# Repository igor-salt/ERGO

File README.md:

Взято отсюда: https://github.com/ergonautkb/one Доработано и исправлено

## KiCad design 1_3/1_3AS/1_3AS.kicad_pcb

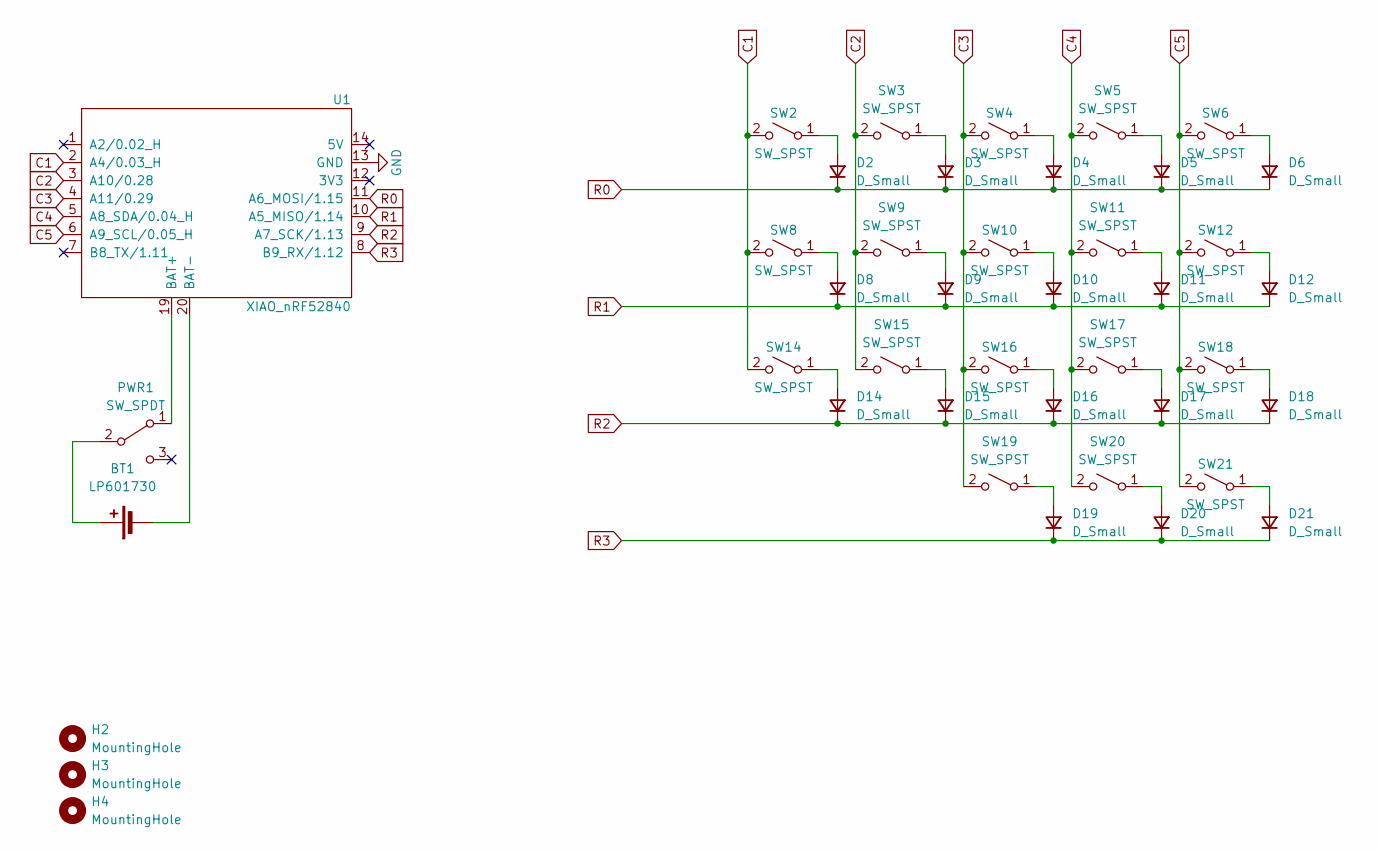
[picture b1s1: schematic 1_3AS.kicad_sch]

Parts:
BT1: LP601730; lp601730
D2, D3, D4, D5, D6, D8, D9, D10, D11, D12, D14, D15, D16, D17, D18, D19, D20, D21: D_Small; Diode_TH_SMD_DUAL
H2, H3, H4: MountingHole; Hole_5.7mm
PWR1: SW_SPDT; MSK-12C02_DUAL
SW2, SW3, SW4, SW5, SW6, SW8, SW9, SW10, SW11, SW12, SW14, SW15, SW16, SW17, SW18, SW19, SW20, SW21: SW_SPST; KS-27_KS-33_Hotswap_1U_DUAL
U1: XIAO_nRF52840; XIAO_nRF52840_DUAL_WINDOW_NO_CAP

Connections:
C1: SW2.2 (B), SW8.2 (B), SW14.2 (B), U1.2 (A4/0.03_H)
C2: SW3.2 (B), SW9.2 (B), SW15.2 (B), U1.3 (A10/0.28)
C3: SW4.2 (B), SW10.2 (B), SW16.2 (B), SW19.2 (B), U1.4 (A11/0.29)
C4: SW5.2 (B), SW11.2 (B), SW17.2 (B), SW20.2 (B), U1.5 (A8_SDA/0.04_H)
C5: SW6.2 (B), SW12.2 (B), SW18.2 (B), SW21.2 (B), U1.6 (A9_SCL/0.05_H)
GND: U1.13 (GND)
unnamed: BT1.1 (+), PWR1.2 (B)
unnamed: BT1.2 (-), U1.20 (BAT-)
unnamed: D2.2 (A), SW2.1 (A)
unnamed: D3.2 (A), SW3.1 (A)
unnamed: D4.2 (A), SW4.1 (A)
unnamed: D5.2 (A), SW5.1 (A)
unnamed: D6.2 (A), SW6.1 (A)
unnamed: D8.2 (A), SW8.1 (A)
unnamed: D9.2 (A), SW9.1 (A)
unnamed: D10.2 (A), SW10.1 (A)
unnamed: D11.2 (A), SW11.1 (A)
unnamed: D12.2 (A), SW12.1 (A)
unnamed: D14.2 (A), SW14.1 (A)
unnamed: D15.2 (A), SW15.1 (A)
unnamed: D16.2 (A), SW16.1 (A)
unnamed: D17.2 (A), SW17.1 (A)
unnamed: D18.2 (A), SW18.1 (A)
unnamed: D19.2 (A), SW19.1 (A)
unnamed: D20.2 (A), SW20.1 (A)
unnamed: D21.2 (A), SW21.1 (A)
unnamed: PWR1.1 (A), U1.19 (BAT+)
R0: D2.1 (K), D3.1 (K), D4.1 (K), D5.1 (K), D6.1 (K), U1.11 (A6_MOSI/1.15)
R1: D8.1 (K), D9.1 (K), D10.1 (K), D11.1 (K), D12.1 (K), U1.10 (A5_MISO/1.14)
R2: D14.1 (K), D15.1 (K), D16.1 (K), D17.1 (K), D18.1 (K), U1.9 (A7_SCK/1.13)
R3: D19.1 (K), D20.1 (K), D21.1 (K), U1.8 (B9_RX/1.12)

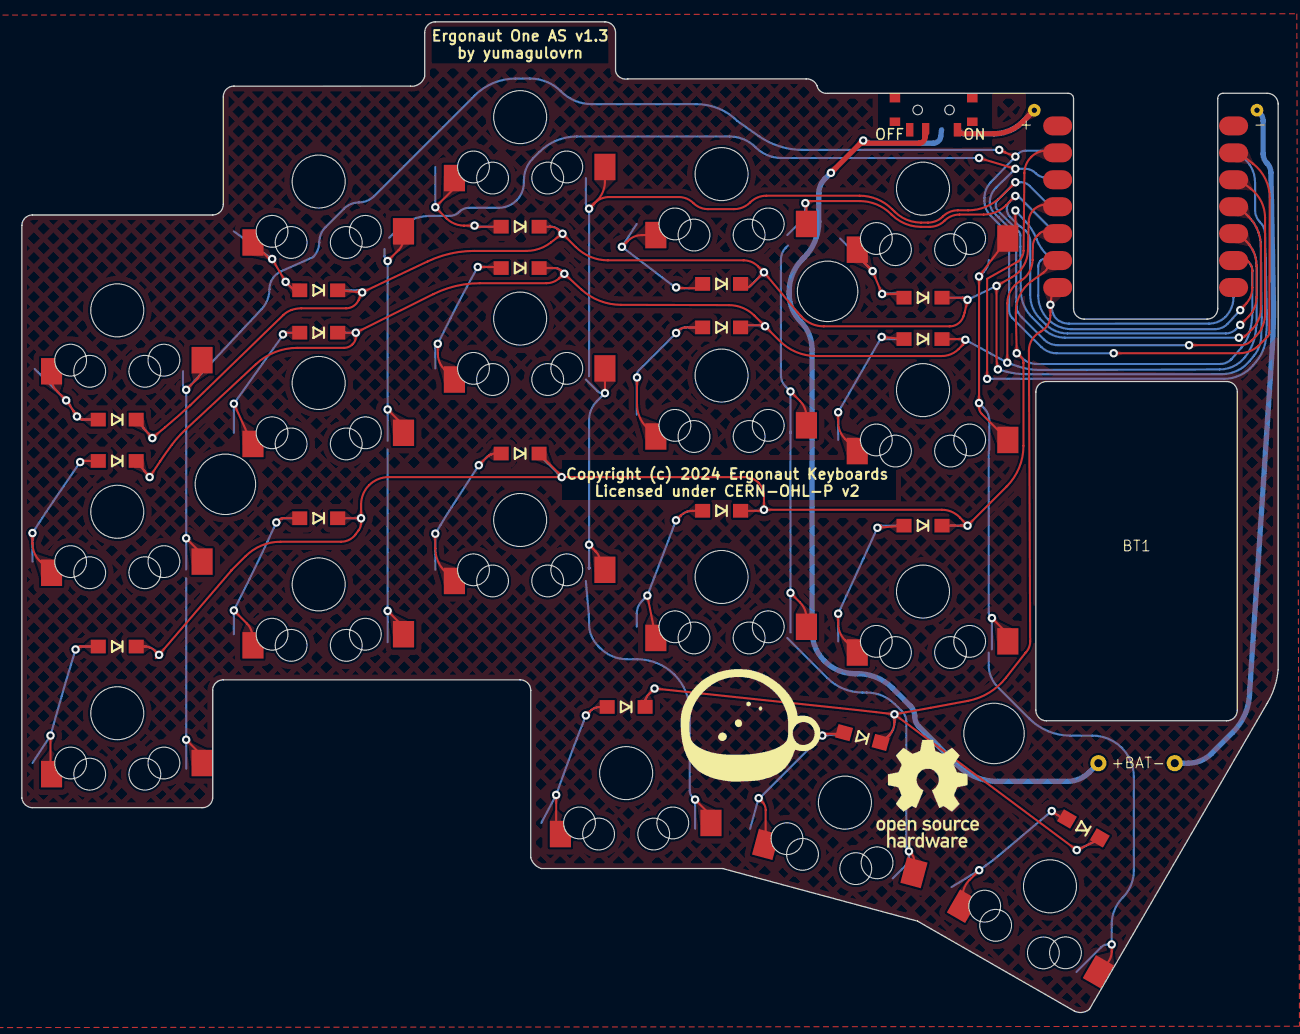
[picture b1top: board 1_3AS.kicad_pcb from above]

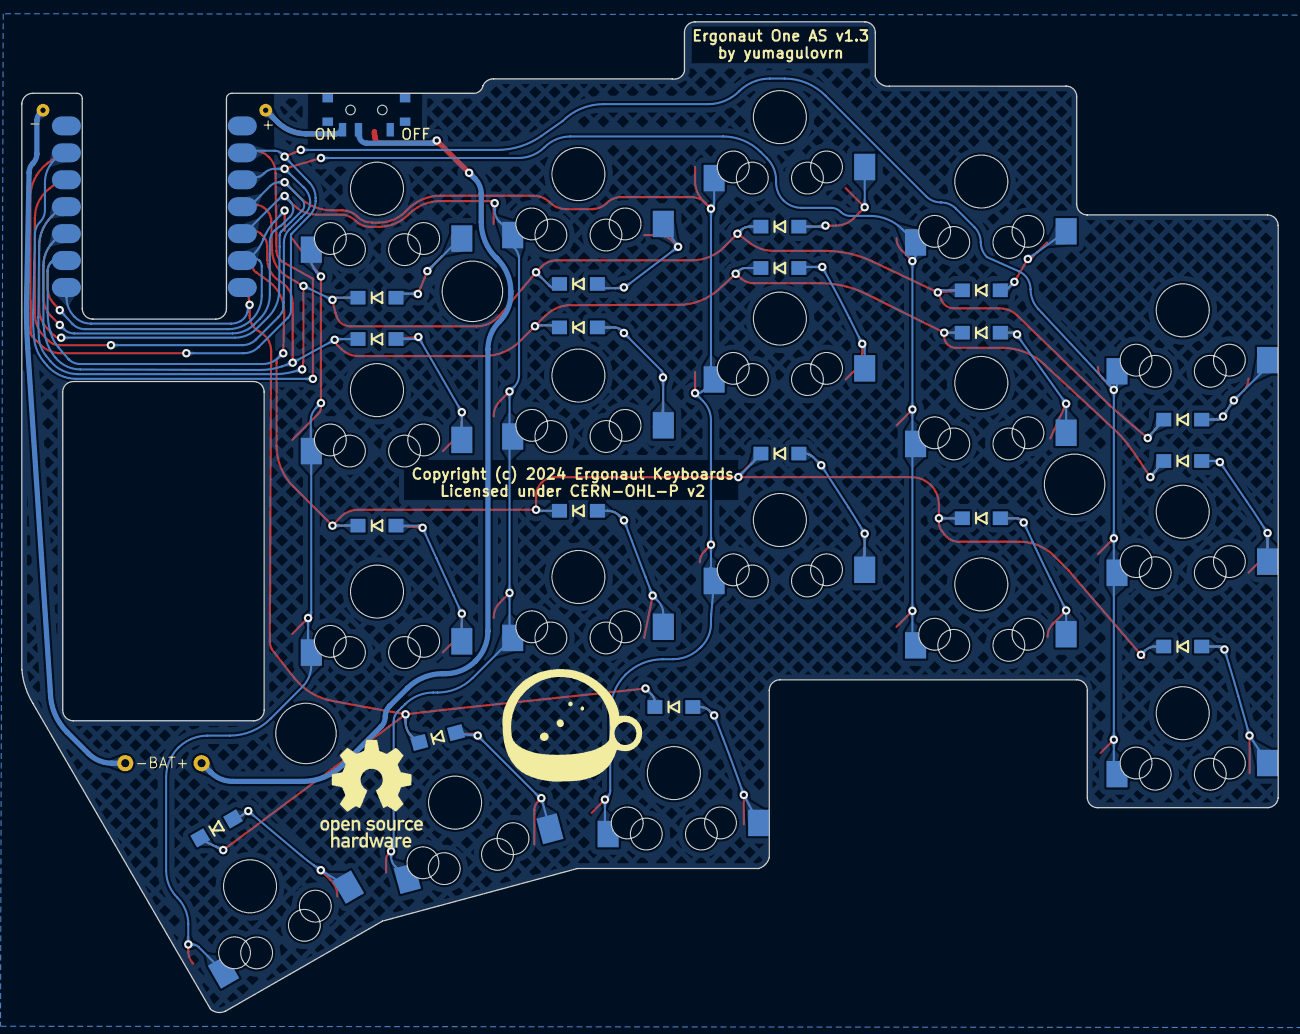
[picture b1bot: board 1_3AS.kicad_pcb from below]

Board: 2 copper layers, 118.5 x 93.4 mm, 42 parts (20 on the bottom side), 30 nets.

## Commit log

2024-10-08 A and AS VERSIONS
2024-10-08 Update 1_3AS.kicad_pcb
    Дырку заделал
2024-10-08 AS add step & gerbers
2024-10-08 A add step & gerbers
2024-10-08 Add 1_3
2024-10-09 1_3 mount hole update
    step & gerbers update
2024-10-09 add 1_3S
2024-10-09 1_3S rebuild
2025-01-19 diode aligvent
2025-01-25 1_3AS chk
2025-01-25 S chk
2025-01-25 AS chk
2025-01-25 1_3 chk
2025-01-25 A chk
2025-01-25 gerbers renew
2025-01-25 Mount Holes & diods alignment
2025-01-25 step files renew
2025-01-29 1_3 tune
2025-01-30 adjust d19,20,21 all

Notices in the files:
1_3/1_3AS/1_3AS.kicad_pcb:
Copyright (c) 2024 Ergonaut Keyboards
Licensed under CERN-OHL-P v2
